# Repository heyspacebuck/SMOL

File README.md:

# SMOL

## **S**lot-in **M**anipulator of **O**utput **L**evels

## (Revision 7)

It's a little PCB to rapidly turn on/off any simple battery-powered circuits. An Atmel ATTiny drives an N-channel MOSFET, which selectively breaks or completes the circuit. The tiny form factor makes it super-simple to install in a battery-powered circuit. Just slot the board between the negative end of the battery and the spring contact, and run a single wire up to the positive battery terminal.

Even with its miniscule form factor, SMOL is designed to be built by surface-mount novices! It has friendly large SMD pads to accept 0603 or 0805 components, and relatively big IC packages (no pitch smaller than 0.90 mm).

If you want to contribute, please do! This thing is here for everyone to experiment with! The circuit is designed in KiCad, just clone/download it and open the project. The project includes self-contained parts and footprints libraries, so it *should* work on any KiCad 5 installation.

## Programming the SMOL
That card-edge connector on the picture above is the [programming interface](programmer.md). Designing this part has been tougher than designing the actual SMOL! But once you get it working, you have the ATTiny10's entire kilobyte of program memory at your disposal. I suggest looking at the [example programs](Code%20examples/readme.md)

## Schematic

## Bill of Materials
| Designation | Description | My Source | My Cost (USD) | Notes |
|:-----------:|-------------|-----------|---------------|-------|
| | Printed circuit board | JLCPCB | $0.125 | See the /gerbs/ folder |
| R1 | 1 MΩ resistor, SMD 0603   | [Digikey](https://www.digikey.com/product-detail/en/vishay-beyschlag/MCT06030C1004FP500/MCT0603-1.00M-CFCT-ND/2607877) | $0.180 | Abbreviated to "1" on the silkscreen. |
| R2 | 180 kΩ resistor, SMD 0603 | [Digikey](https://www.digikey.com/product-detail/en/yageo/RC0603FR-07180KL/311-180KHRCT-ND/729942) | $0.015 | Abbreviated to "2" on the silkscreen. |
| R3 | 20 kΩ resistor, SMD 0603  | [Digikey](https://www.digikey.com/product-detail/en/panasonic-electronic-components/ERJ-3EKF2002V/P20.0KHCT-ND/198237) | $0.100 | Abbreviated to "3" on the silkscreen. |
| R4 | 200 Ω resistor, SMD 0603  | [Digikey](https://www.digikey.com/product-detail/en/panasonic-electronic-components/ERJ-3EKF2000V/P200HCT-ND/198240) | $0.100 | Abbreviated to "4" on the silkscreen. |
| C1, C2 | 10 μF capacitor, SMD 0603 | [Digikey](https://www.digikey.com/product-detail/en/murata-electronics-north-america/ZRB18AR61C106ME01L/490-10990-1-ND/5321191) | $0.365 | Both are abbreviated to "C" on the silkscreen. |
| L1 | 4.7 μH inductor, SMD 0603 | [Digikey](https://www.digikey.com/product-detail/en/tdk-corporation/MLF1608A4R7KTA00/445-1021-1-ND/504419) | $0.200 | I should probably use one that's rated to more than 30 mA. Abbreviated to "L" on the silkscreen. |
| Q1 | N-channel MOSFET, SMD SOT-523 | [Digikey](https://www.digikey.com/product-detail/en/diodes-incorporated/DMG1012T-7/DMG1012T-7DICT-ND/2181232) | $0.360 | [Datasheet](https://www.diodes.com/assets/Datasheets/ds31783.pdf). Abbreviated to "Q" on the silkscreen. |
| D1 | General purpose diode, SMD SOT-523 | [Digikey](https://www.digikey.com/product-detail/en/micro-commercial-co/MMBD4448HT-TP/MMBD4448HT-TPMSCT-ND/2041561) | $0.270 | [Datasheet](http://www.mccsemi.com/up_pdf/MMBD4448HT_HTC_HTA_HTS%28SOT-523%29.pdf). This part is optional but protects the board from motor back-EMF. Abbreviated to "D" on the silkscreen. |
| U1 | TLV61220 DC-DC boost converter, SMD SOT-23-6 | [Digikey](https://www.digikey.com/product-detail/en/texas-instruments/TLV61220DBVR/296-30547-1-ND/3458120) | $0.900 | [Datasheet](http://www.ti.com/lit/ds/symlink/tlv61220.pdf) |
| U2 | ATTiny10 8-bit microcontroller, SMD SOT-23-6 Narrow | [Digikey](https://www.digikey.com/product-detail/en/microchip-technology/ATTINY10-TSHR/ATTINY10-TSHRCT-ND/2136158) | $0.340 | [Datasheet](http://ww1.microchip.com/downloads/en/DeviceDoc/Atmel-8127-AVR-8-bit-Microcontroller-ATtiny4-ATtiny5-ATtiny9-ATtiny10_Datasheet.pdf). Uses the TPI programming interface, which is a pain. |
| | Approx. 5 cm of 30AWG wire | Anywhere | $0.000 | Solder to TP1 and attach the other end to the battery's positive terminal. Soldering an old battery clip to the end helps make a reliable connection. |
| | Approx. 1 cm of stiff bare wire | Anywhere | $0.000 | Solder to TP2 and bend so the battery's negative terminal rests on it but doesn't short any traces. |
| | Conformal coating (or other insulating material) | Anywhere | $0.000 | Optional but recommended. Insulate the board so the stiff bare wire can't short anything. |

TOTAL COST PER BOARD: approx. $3.50

## Revision history
SMOL has changed a lot since I first got the idea. Amazingly, it hasn't gotten bigger. [For a commentated revision history: click here.](revisions.md)

## Contact info:
- E-mail heyspacebuck at gmail
- Twitter @heyspacebuck
- Telegram @spacebuck

## To Do:
- Write better assembly instructions
- Add pictures + video
- Post sample AVR code
- Add OSHW certification mark

------

IT'S SO SMOL

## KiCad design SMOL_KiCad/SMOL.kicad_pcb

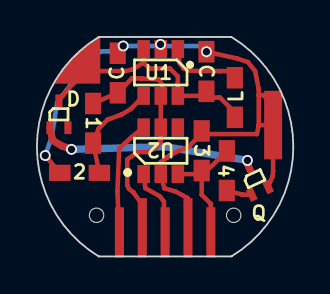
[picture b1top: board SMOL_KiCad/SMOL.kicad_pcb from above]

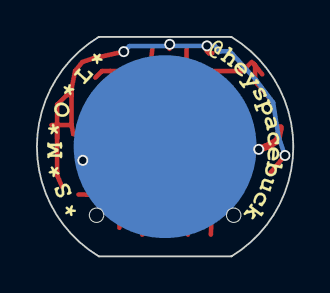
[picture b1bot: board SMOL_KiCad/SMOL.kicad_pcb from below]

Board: 2 copper layers, 14.2 x 12.2 mm, 19 parts (3 on the bottom side), 10 nets.

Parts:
1: 1MΩ; 0603_HandSoldering
2: 180kΩ; 0603_HandSoldering
3: 20kΩ; 0603_HandSoldering
4: 1kΩ; 0603_HandSoldering
C: 10μF; 0603_HandSoldering
C#2: 10μF; 0603_HandSoldering
D: D_SOT523; SOT523_HandSoldering
GFX1: credits2-name
GFX2: credits2-title
HOLE1, HOLE2: SolderWirePad_single_2mmDrill
J1: Conn_01x05; edgeconn
L: 4.7μH; 0603_HandSoldering
Q: Q_NMOS_GSD; SOT523_HandSoldering
TP1: TEST; Anchor_Pad
TP2: TEST; SPRING_ANCHOR
TP3: TEST; SPRING_LANDING
U1: TLV61220; SuperSOT-6
U2: ATTINY10-TS; SuperSOT-6

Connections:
/Anode: 2.2, 3.1, C.2, C#2.2, J1.4, Q.2, TP2.1, U1.2, U2.2
/Cathode: C.1, D.3, L.1, TP1.1, U1.3, U1.6
/Spring_Contact: D.1, Q.3, TP3.1
/μC_Vcc: 1.1, C#2.1, J1.2, U1.5, U2.5
unnamed: J1.1, U2.6
unnamed: J1.3, U2.1
unnamed: 3.2, 4.1, J1.5, U2.3
unnamed: L.2, U1.1
unnamed: 4.2, Q.1
unnamed: 1.2, 2.1, U1.4

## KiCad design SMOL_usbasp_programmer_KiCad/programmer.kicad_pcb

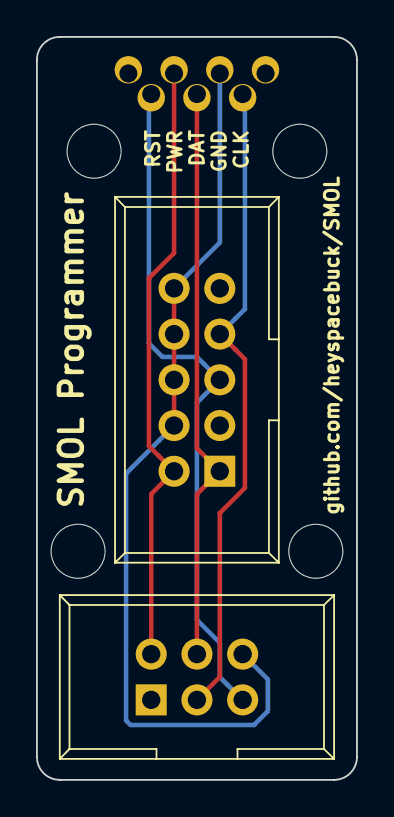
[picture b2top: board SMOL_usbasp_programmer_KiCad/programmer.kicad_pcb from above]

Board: 2 copper layers, 17.8 x 41.3 mm, 9 parts (0 on the bottom side), 5 nets.

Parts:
CON1: AVR-TPI-6; IDC_Header_Straight_6pins
CON2: AVR-ISP-10; IDC_Header_Straight_10pins
HOLE1, HOLE2, HOLE3, HOLE4: MountingHole_3.2mm_M3
HOLE5, HOLE6: SolderWirePad_single_1mmDrill
J2: Conn_01x05; edgeconn

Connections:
/att_clk: CON1.3, CON2.7, J2.5
/att_data: CON1.4, CON2.1, J2.3
/att_reset: CON1.5, CON2.5, J2.1
/pwr: CON1.2, CON2.2, J2.2
GNDREF: CON1.6, CON2.4, CON2.6, CON2.8, CON2.10, J2.4

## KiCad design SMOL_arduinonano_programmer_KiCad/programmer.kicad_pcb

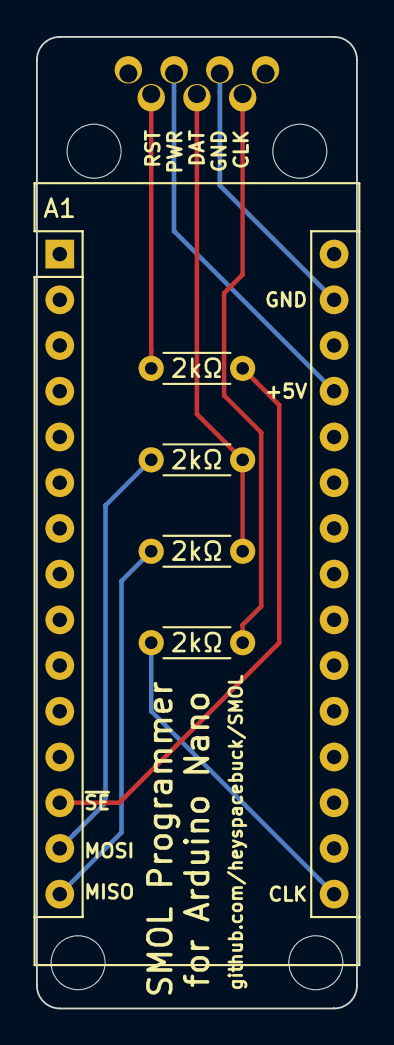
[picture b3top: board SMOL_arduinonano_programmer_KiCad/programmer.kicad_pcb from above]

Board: 2 copper layers, 17.8 x 54.0 mm, 12 parts (0 on the bottom side), 9 nets.

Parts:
2kΩ, 2kΩ#2, 2kΩ#3, 2kΩ#4: 2k; R_Axial_DIN0204_L3.6mm_D1.6mm_P5.08mm_Horizontal
A1: Arduino_Nano_v3.x; Arduino_Nano
HOLE1, HOLE2, HOLE3, HOLE4: MountingHole_3.2mm_M3
HOLE5, HOLE6: SolderWirePad_single_1mmDrill
J2: Conn_01x05; edgeconn

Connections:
/att_clk: 2kΩ#4.2, J2.5
/att_data: 2kΩ#2.2, 2kΩ#3.2, J2.3
/att_reset: 2kΩ.2, J2.1
/prog_clk: 2kΩ#4.1, A1.16
/prog_miso: 2kΩ#2.1, A1.14
/prog_mosi: 2kΩ#3.1, A1.15
/prog_reset: 2kΩ.1, A1.13
/pwr: A1.27, J2.2
GNDREF: A1.4, A1.29, J2.4

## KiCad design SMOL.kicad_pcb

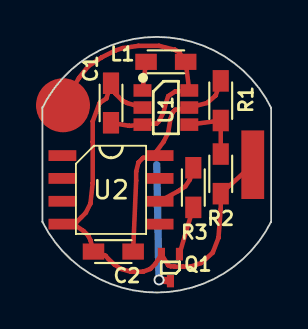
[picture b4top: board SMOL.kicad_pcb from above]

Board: 2 copper layers, 12.7 x 14.2 mm, 12 parts (1 on the bottom side), 8 nets.

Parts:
C1, C2: 10μ; 0603_HandSoldering
L1: 4.7μ; 0603_HandSoldering
Q1: Q_NMOS_GSD; SOT523_HandSoldering
R1: 1M; 0603_HandSoldering
R2: 180k; 0603_HandSoldering
R3: 1k; 0603_HandSoldering
TP1: TEST; Anchor_Pad
TP2: TEST; SPRING_ANCHOR
TP3: TEST; SPRING_LANDING
U1: TLV61220; SuperSOT-6
U2: ATTINY13-20SSU; SOIC-8_3.9x4.9mm_Pitch1.27mm

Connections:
/Anode: C1.2, C2.2, Q1.2, R2.2, TP2.1, U1.2, U2.4
/Cathode: C1.1, L1.1, TP1.1, U1.3, U1.6
/Spring_Contact: Q1.3, TP3.1
/μC_Vcc: C2.1, R1.1, U1.5, U2.8
unnamed: L1.2, U1.1
unnamed: Q1.1, R3.1
unnamed: R1.2, R2.1, U1.4
unnamed: R3.2, U2.6

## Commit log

2018-06-22 Repo created; missing readme
2018-06-23 very minor change in schematic; the motor M was asymmetrical
2018-06-25 Hacky fix to board outline; fixed Q1's 3d representation
2018-06-25 Updated gerbers to reflect the edge cuts change (maybe now JLCPCB will accept my order)
2018-06-25 Moved KiCad project to its own folder
2018-06-25 Added some images to the repo
2018-07-22 Rearranged components, set up for ATTiny10 instead of 13
2018-07-22 Oops, put gerbers in the wrong directory
2018-07-31 First release of the ATTiny10 version.
2018-07-31 Added diode and re-wired output from U2
2018-07-31 Forgot to remove a global library
2018-07-31 Fixed readme markdown
2018-10-17 Updated schematic and libs to KiCad 5.x
2018-10-17 Wrapped up(?) update to KiCad 5.0
2018-10-28 Preparing to update PCB and gerbs for next round of development
2018-10-31 Revision 5: added an FFC connector for easier programming (at the expense of my commitment to hand-solderability)
2018-11-04 Revision 6 - a card-edge connector with a plug-in programmer
2018-11-04 schematic update for readme
2018-11-09 Tweaked the bottom silkscreen and moved vias to make it legible
2018-12-21 Updated gerbs, added folder for AVR programs
2019-02-26 Working toward new release, updating images and documents
2019-02-26 Update spinning render
2019-02-26 Updated documentation
2019-03-22 re-jigging the form factor of circuit revision 6
2019-03-22 re-sized mounting holes to fit M1.4 bolts, like in japanese watches. Everyone has m1.4 bolts handy, right?
2019-04-08 overhauled programmer design; going to try pogo pins and an arduino nano shield
2019-04-09 Another variant programmer to test: this one's a sandwich
2019-04-27 Revert "Another variant programmer to test: this one's a sandwich"
    This reverts commit 6c5b6402040f09fce85967fa71119872cc965c26.
2019-04-27 Reverted the 'sandwich' programmer; tweaked the pogo-pin programmer
2019-04-29 Revision 6c - use pogo pins for programming AND alignment
2019-05-17 Updating in anticipation of merge
2019-05-20 FINALLY fixed the anchor points for mounting holes on SMOL and programmers. Added OSHW logo to library, just in case....
2019-05-21 Backpedalling on calling the minor changes 'rev. 6c', possibly because I'm jetlagged and it's 4:30 a.m.
2019-05-25 Updated the USBasp programmer; updated programmer silkscreens
2019-05-25 Updated images
2019-05-25 Began assembly instructions
2019-05-25 fixed an upside-down image
2019-05-25 Cleaned up Gerbers, updated programmer images
2019-05-25 Updated two more images
2019-05-25 Fix image name in markdown
2019-05-25 small cosmetic change to Arduino Nano programmer
2019-05-29 Updated example code
2019-05-30 Fix broken link to examples
2019-06-13 Added a random number generator! Cleaned up code examples in general
2019-06-20 Revision seven! Added a small resistor to protect the MOSFET.
2019-06-20 Revision 7 gerbers
2019-06-20 Update documentation for R7
2019-06-20 Update BOM
